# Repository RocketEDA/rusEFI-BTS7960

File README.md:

# BTS7960 Module Adapter

RusEFI's implementation of the H-bridge requires 3 pins, PWM, DIR, and EN. This is analogous to the TLE9201SG. On amazon and sorts, you can find these inexpensive 43A H bridge using the obsolete BTS7960. This project aims to create an adapter for them to work with rusEFI.

[source](https://www.ovaga.com/blog/transistor/bts7960-motor-driver-datasheet-and-circuit-diagram)

# Connection

The board stacks on as pictured. DIR/DIS/PWM correlate to rusEFI's 3/2 wire pins originally intended for the TLE9201SG. The DIS pin connection is not needed for 2 wire operation.

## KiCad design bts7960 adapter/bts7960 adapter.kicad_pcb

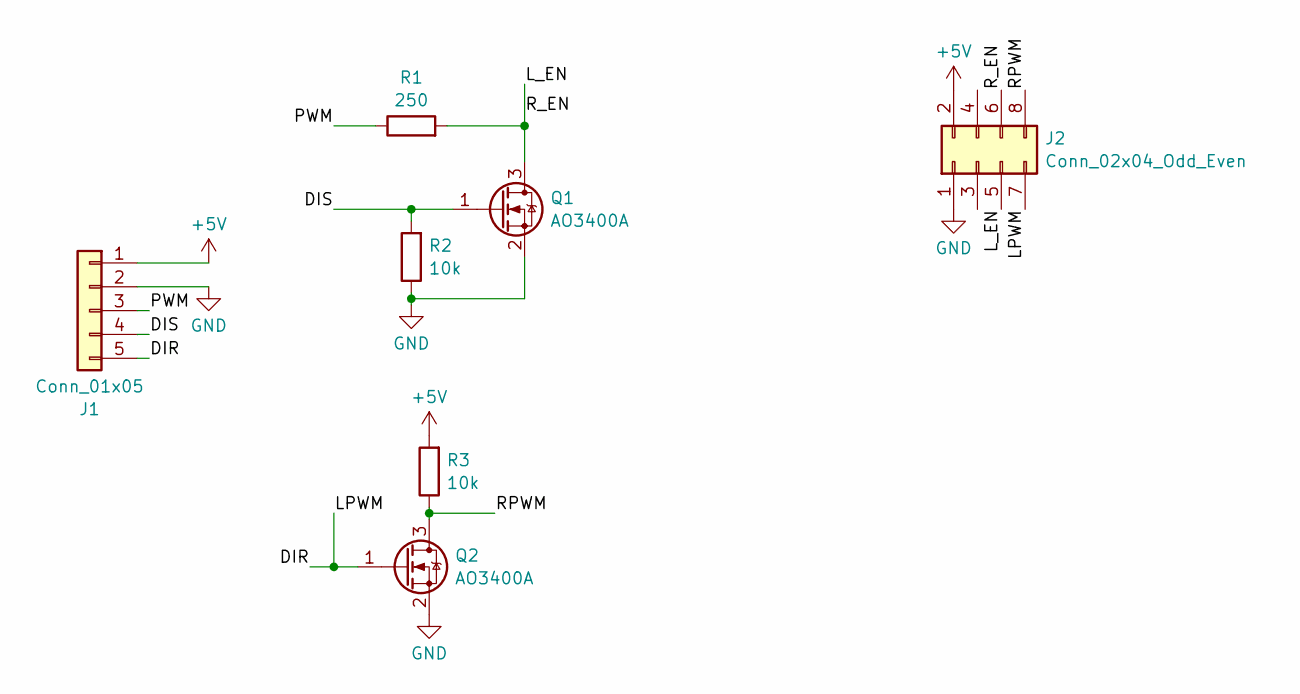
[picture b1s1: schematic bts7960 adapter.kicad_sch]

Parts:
J1: Conn_01x05; PinHeader_1x05_P2.54mm_Vertical
J2: Conn_02x04_Odd_Even; PinHeader_2x04_P2.54mm_Vertical
Q1, Q2: AO3400A; SOT-23
R1: 250; R_0603_1608Metric_Pad0.98x0.95mm_HandSolder
R2, R3: 10k; R_0603_1608Metric_Pad0.98x0.95mm_HandSolder

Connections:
+5V: J1.1, J2.2, R3.2
/DIR: J1.5, J2.7, Q2.1 (G)
/DIS: J1.4, Q1.1 (G), R2.2
/L_EN: J2.5, J2.6, Q1.3 (D), R1.2
/PWM: J1.3, R1.1
/RPWM: J2.8, Q2.3 (D), R3.1
GND: J1.2, J2.1, Q1.2 (S), Q2.2 (S), R2.1

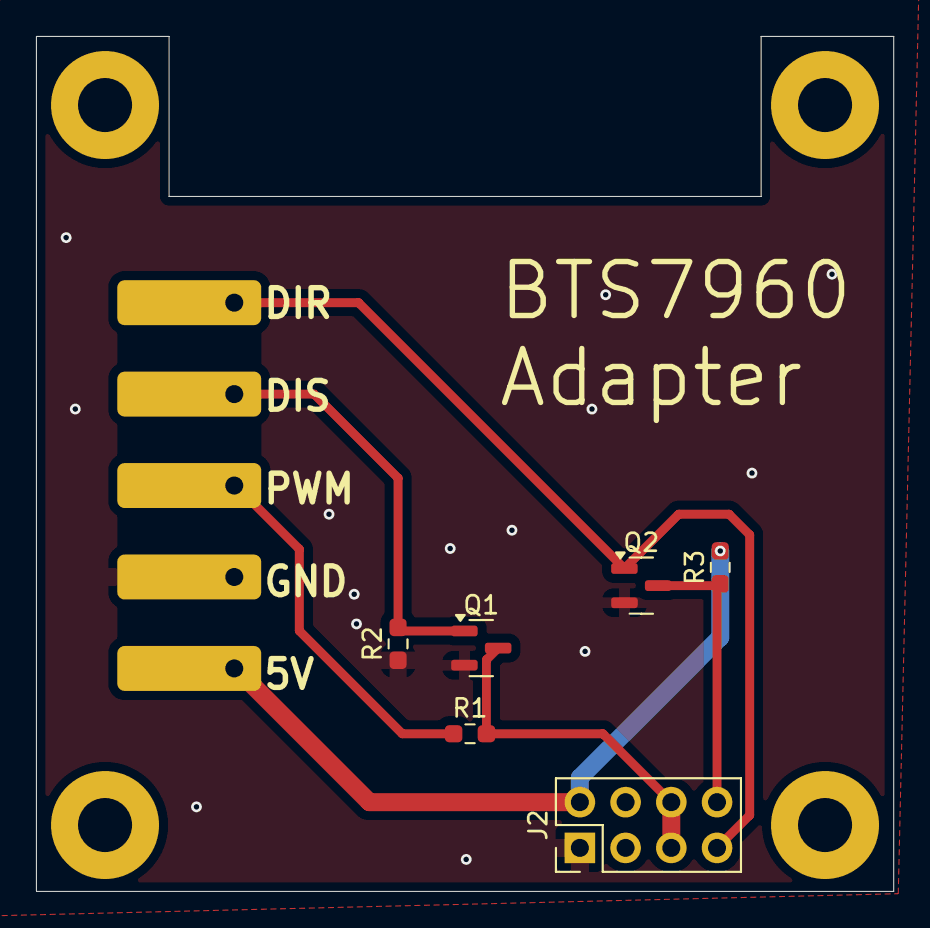
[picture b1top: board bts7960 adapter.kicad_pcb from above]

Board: 2 copper layers, 47.6 x 47.5 mm, 7 parts (0 on the bottom side), 7 nets.

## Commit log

2025-02-23 done
